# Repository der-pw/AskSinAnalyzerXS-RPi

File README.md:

# AskSinAnalyzerXS-RPi     
Raspberry Pi Addon PCB für den [AskSinAnalyzerXS](https://github.com/psi-4ward/AskSinAnalyzerXS).  
Dieser wird einfach auf die GPIO-Leist gesteckt.  
Es kann der Standard Sketch (AskSinSniffer328P) aus dem [AskSinAnalyzer](https://github.com/jp112sdl/AskSinAnalyzer) Repo von Jérôme geflashed werden.  

Im Prinzip kann der AskSinAnalyzerXS-RPi nach dem Zusammenbau mit einem Programmer (FTDI) verbunden und geflashed werden.
Der 3V Jumper kann gebrückt werden, damit die Stromversorgung vom FTDI erfolgt. DTR kann ebenfalls gebrückt werden um Reset auszulösen.
Der 0.1uF in der DTR Strecke ist nicht auf dem PCB vorhanden und sollte ins Verbindungskabel integriert werden. Alternativ kann auch Reset im richtigen Moment kurz gegen GND gebrückt werden.  
Nach erfolgreichem Flashvorgang und ersten Ausgaben auf der serielen Konsole, müssen die Lötbrücken wieder entfernt werden, bevor die Platine auf den Raspberry Pi gesteckt wird.

Folgender Tipp ist möglicherweise hilfreich, bei Verwendung der seriellen Schnittstellen auf dem RPi.  
https://homematic-forum.de/forum/viewtopic.php?f=76&t=56395&start=70#p569429 

Dieses Werk ist lizenziert unter einer [Creative Commons Namensnennung - Nicht-kommerziell - Weitergabe unter gleichen Bedingungen 4.0 International Lizenz](http://creativecommons.org/licenses/by-nc-sa/4.0/).

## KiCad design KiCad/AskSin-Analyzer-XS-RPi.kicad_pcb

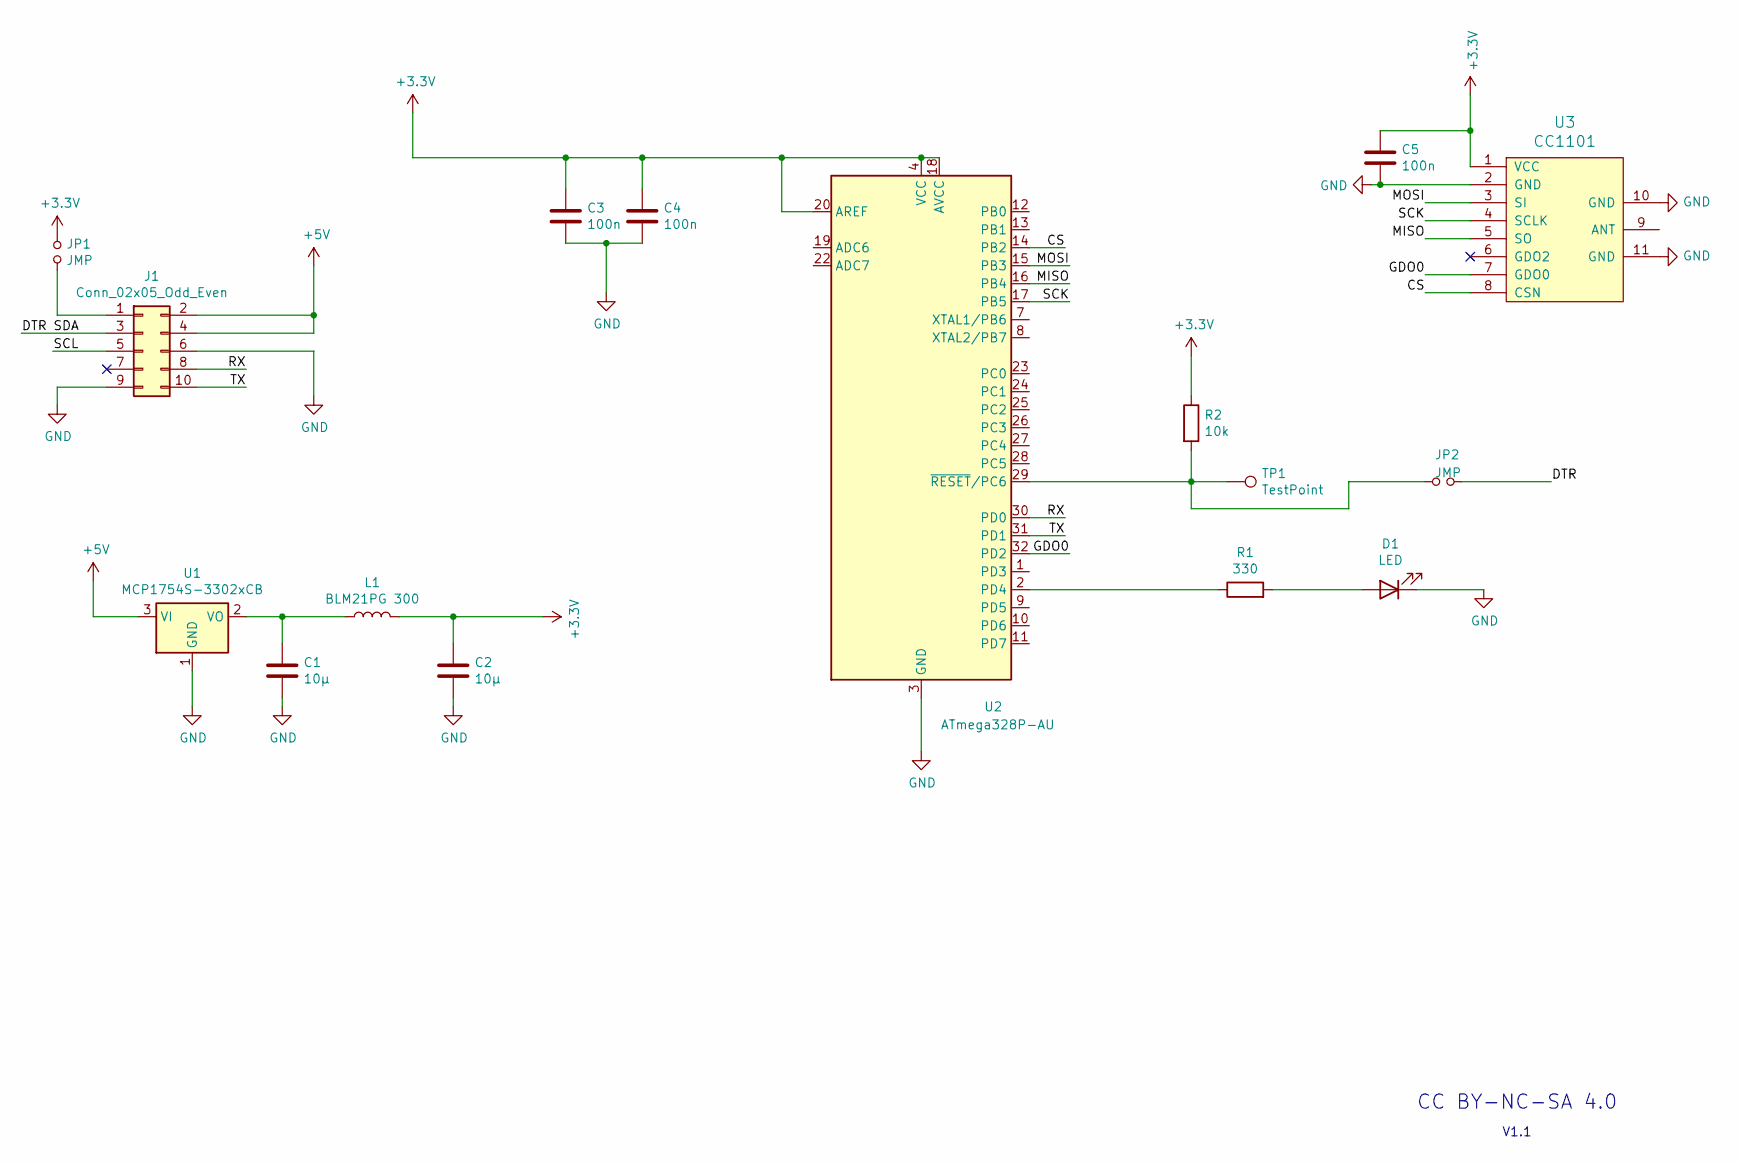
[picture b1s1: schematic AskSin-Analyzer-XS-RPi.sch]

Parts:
C1, C2: 10µ; C_0805_2012Metric_Pad1.15x1.40mm_HandSolder
C3, C4, C5: 100n; C_0805_2012Metric_Pad1.15x1.40mm_HandSolder
D1: LED; LED_0805_2012Metric_Pad1.15x1.40mm_HandSolder
J1: Conn_02x05_Odd_Even; PinHeader_2x05_P2.54mm_Vertical
JP1, JP2: JMP; my_mini_Jumper
L1: BLM21PG 300; L_0805_2012Metric_Pad1.15x1.40mm_HandSolder
R1: 330; R_0805_2012Metric_Pad1.15x1.40mm_HandSolder
R2: 10k; R_0805_2012Metric_Pad1.15x1.40mm_HandSolder
TP1: TestPoint; TestPoint_Pad_2.0x2.0mm
U1: MCP1754S-3302xCB; SOT-23
U2: ATmega328P-AU; TQFP-32_7x7mm_P0.8mm
U3: CC1101; CC1101_Module_HM-Sensor

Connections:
+3V3: C2.1, C3.1, C4.1, C5.1, JP1.1, L1.2, R2.1, U2.4 (VCC), U2.6 (VCC), U2.18 (AVCC), U2.20 (AREF), U3.1 (VCC)
+5V: J1.2, J1.4, U1.3 (VI)
/CS: U2.14 (PB2), U3.8 (CSN)
/DTR: J1.3, JP2.2
/GDO0: U2.32 (PD2), U3.7 (GDO0)
/MISO: U2.16 (PB4), U3.5 (SO)
/MOSI: U2.15 (PB3), U3.3 (SI)
/RX: J1.8, U2.30 (PD0)
/SCK: U2.17 (PB5), U3.4 (SCLK)
/SCL: J1.5
/TX: J1.10, U2.31 (PD1)
GND: C1.2, C2.2, C3.2, C4.2, C5.2, D1.1 (K), J1.6, J1.9, U1.1 (GND), U2.3 (GND), U2.5 (GND), U2.21 (GND), U3.2 (GND), U3.10 (GND), U3.11 (GND)
unnamed: C1.1, L1.1, U1.2 (VO)
unnamed: D1.2 (A), R1.2
unnamed: J1.1, JP1.2
unnamed: JP2.1, R2.2, TP1.1, U2.29 (~RESET~/PC6)
unnamed: R1.1, U2.2 (PD4)

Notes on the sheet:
CC BY-NC-SA 4.0
V1.1

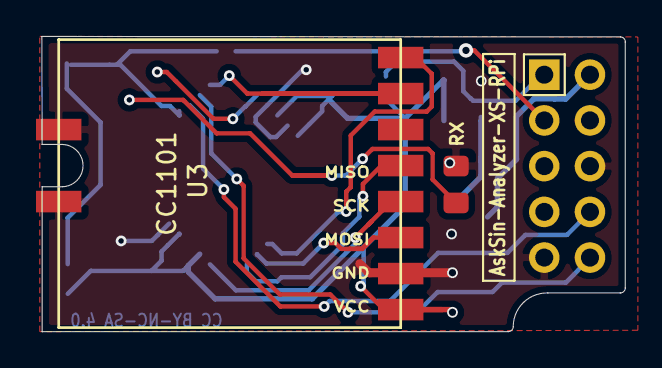
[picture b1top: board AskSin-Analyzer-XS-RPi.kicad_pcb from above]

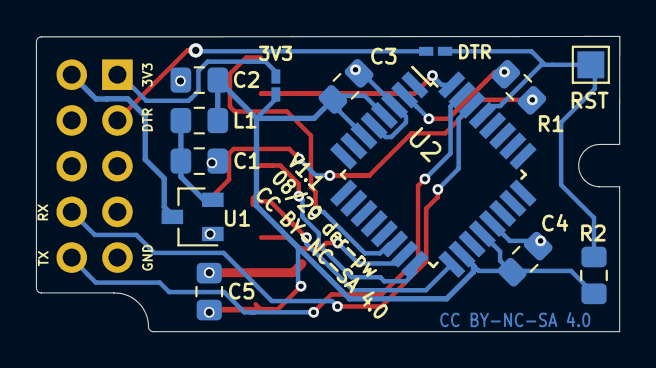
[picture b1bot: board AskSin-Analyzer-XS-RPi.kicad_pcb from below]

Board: 2 copper layers, 32.4 x 16.4 mm, 16 parts (13 on the bottom side), 16 nets.

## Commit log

2020-11-13 upload
2020-12-14 Update README.md
    typos

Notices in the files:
README.md:
License: CC BY-NC-SA 4.0
Creative Commons Lizenzvertrag
